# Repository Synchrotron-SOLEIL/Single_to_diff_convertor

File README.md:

Single to Differential Convertors
=================================
Analog Single to Differential Convertors for testing purpose.

Released under GNU GPL license.

Synchrotron SOLEIL's name and logo cannot be used without permission.

----------

http://www.synchrotron-soleil.fr/

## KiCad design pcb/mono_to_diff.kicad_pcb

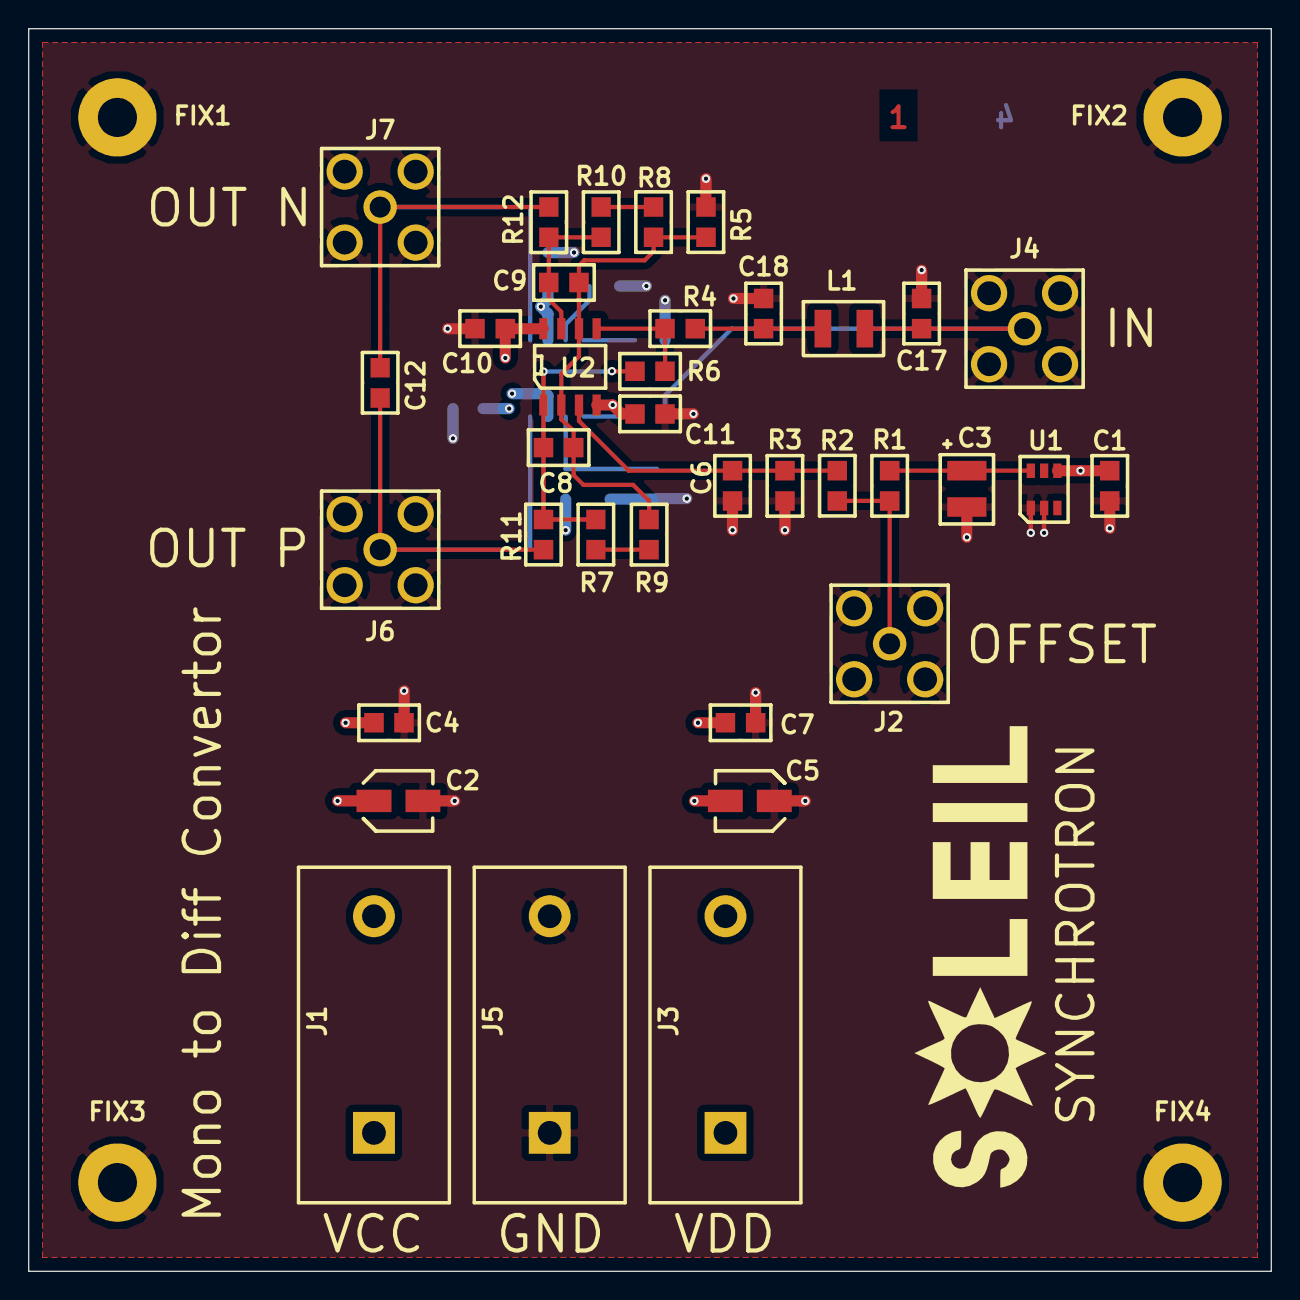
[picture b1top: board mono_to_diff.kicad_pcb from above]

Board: 4 copper layers, 88.9 x 88.9 mm, 51 parts (0 on the bottom side), 22 nets.

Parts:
C1, C10, C11, C12, C15, C16: 10nF-50V-10p-Ceramic-0805; SOLEIL-0805
C2, C5: 10uF-16V-20p-Al-TypeB; SOLEIL-TYPEB
C3: 2u2F-20V-10p-Tantalum-1210; SOLEIL-PC-B
C4, C7, C13, C14: 100nF-50V-10p-Ceramic-0805; SOLEIL-0805
C6: 1nF-50V-10p-Ceramic-0805; SOLEIL-0805
C8, C9: 5pF-50V-10p-Ceramic-0805; SOLEIL-0805
C17, C18: 2200pF-50V-5p-Ceramic-0805; SOLEIL-0805
FIX1, FIX2, FIX3, FIX4: D_2mm8; SOLEIL-D_2mm8
J1: 24.243.1; SOLEIL-24_243
J2, J4, J6, J7: 132134; SOLEIL-SMA-132134
J3: 24.243.5; SOLEIL-24_243
J5: 24.243.2; SOLEIL-24_243
L1: 10uH-140mA-5p-36MHz-1210; SOLEIL-1210
R1, R17, R18: 0R-0.125W-1P-0805; SOLEIL-0805
R2: 2K37-0.125W-1P-0805; SOLEIL-0805
R3, R14: 1K-0.125W-1P-0805; SOLEIL-0805
R4: 2K2-0.125W-1P-0805; SOLEIL-0805
R5: 470R-0.125W-1P-0805; SOLEIL-0805
R6: 499R-0.125W-1P-0805; SOLEIL-0805
R7, R8: 215R-0.125W-1P-0805; SOLEIL-0805
R9, R10: 1R2-0.125W-1P-0805; SOLEIL-0805
R11, R12: 51R-0.125W-1P-0805; SOLEIL-0805
R13: 1K87-0.125W-1P-0805; SOLEIL-0805
R15, R16: 1K58-0.125W-1P-0805; SOLEIL-0805
U1: LT6656ACS6-1.25; SOLEIL-SOT23-6
U2: LTC6241HVCS8; SOLEIL-SOIC8NB
U3: LT6600CS8-2.5; SOLEIL-SOIC8NB

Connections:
/OUT_N: C12.2, J7.1, R12.1, R18.2
/OUT_P: C12.1, J6.1, R11.1, R17.2
GND: C1.2, C2.2, C3.2, C4.2, C5.1, C6.2, C7.2, C10.2, C11.2, C13.2, C14.2, C15.2, C16.2, C17.2, C18.2, FIX1.1, FIX2.1, FIX3.1, FIX4.1, J2.2, J2.3, J2.4, J2.5, J4.2, J4.3, J4.4, J4.5, J5.1, J5.2, J6.2, J6.3, J6.4, J6.5, J7.2, J7.3, J7.4, J7.5, R3.2, R5.2, R14.2, R16.1, U1.1, U1.2
unnamed: C3.1, R1.1, U1.6
unnamed: C6.1, R2.2, R3.1, U2.3
unnamed: C8.1, R6.1, R9.2, R11.2, U2.1
unnamed: C8.2, C9.2, R5.1, R7.1, R8.1, U2.2, U2.6
unnamed: C9.1, R10.2, R12.2, U2.7
unnamed: C13.1, R13.2, R14.1, U3.2
unnamed: C14.1, U3.7
unnamed: C17.1, J4.1, L1.1, R15.1
unnamed: C18.1, L1.2, R4.2
unnamed: J2.1, R1.2, R2.1
unnamed: R4.1, R6.2, U2.5
unnamed: R7.2, R9.1
unnamed: R8.2, R10.1
unnamed: R15.2, U3.1
unnamed: R16.2, U3.8
unnamed: R17.1, U3.4
unnamed: R18.1, U3.5
VCC: C1.1, C2.1, C4.1, C10.1, C15.1, J1.1, J1.2, R13.1, U1.4, U2.8, U3.3
VDD: C5.2, C7.1, C11.1, C16.1, J3.1, J3.2, U2.4, U3.6

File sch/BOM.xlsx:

Single to Differential Convertors
JP Ricaud
42179
Ref | Manufacturer | Manufacturer ref | Supplier | Supplier ref | Value | Description 1 | Description 1 | Description 3 | Case | Price | Qty
L1 | Panasonic | ELJFA100JF | Farnell | 1198456 | 10uH | 140mA | 5% | 36MHz | 1210 | 0.09 | 1
C13 | KEMET | C0805F104K5RACTU | Farnell | 1288272RL | 100nF | 50V | 10% | X7R | 0805 | 0.28000000000000003 | 1
C14 | KEMET | C0805F104K5RACTU | Farnell | 1288272RL | 100nF | 50V | 10% | X7R | 0805 | 0.28000000000000003 | 1
C4 | KEMET | C0805F104K5RACTU | Farnell | 1288272RL | 100nF | 50V | 10% | X7R | 0805 | 0.28000000000000003 | 1
C7 | KEMET | C0805F104K5RACTU | Farnell | 1288272RL | 100nF | 50V | 10% | X7R | 0805 | 0.28000000000000003 | 1
U2 | LINEAR TECHNOLOGY | LTC6241HVCS8#PBF | Farnell | 1330970 |  | - | - | - | SOIC8 | 5.28 | 1
C6 | KEMET | C0805C102K5RACTU | Farnell | 1414660 | 1nF | 50V | 10% | X7R | 0805 | 3.2000000000000001E-2 | 1
C1 | KEMET | C0805C103K5RACTU | Farnell | 1414662 | 10nF | 50V | 10% | X7R | 0805 | 3.2000000000000001E-2 | 1
C10 | KEMET | C0805C103K5RACTU | Farnell | 1414662 | 10nF | 50V | 10% | X7R | 0805 | 3.2000000000000001E-2 | 1
C11 | KEMET | C0805C103K5RACTU | Farnell | 1414662 | 10nF | 50V | 10% | X7R | 0805 | 3.2000000000000001E-2 | 1
C12 | KEMET | C0805C103K5RACTU | Farnell | 1414662 | 10nF | 50V | 10% | X7R | 0805 | 3.2000000000000001E-2 | 0
C15 | KEMET | C0805C103K5RACTU | Farnell | 1414662 | 10nF | 50V | 10% | X7R | 0805 | 3.2000000000000001E-2 | 1
C16 | KEMET | C0805C103K5RACTU | Farnell | 1414662 | 10nF | 50V | 10% | X7R | 0805 | 3.2000000000000001E-2 | 1
R1 | Vishay | CRCW08050000Z0EA | Farnell | 1469846RL | 0R | 0.125W | 1% | Thick Film | 0805 | 2.1000000000000001E-2 | 1
R17 | Vishay | CRCW08050000Z0EA | Farnell | 1469846RL | 0R | 0.125W | 1% | Thick Film | 0805 | 2.1000000000000001E-2 | 1
R18 | Vishay | CRCW08050000Z0EA | Farnell | 1469846RL | 0R | 0.125W | 1% | Thick Film | 0805 | 2.1000000000000001E-2 | 1
R4 | Vishay | CRCW08052K20FKEA | Farnell | 1469887RL | 2K2 | 0.125W | 1% | Thick Film | 0805 | 2.1999999999999999E-2 | 1
R5 | Vishay | CRCW0805470RFKEA | Farnell | 1469932 | 470R | 0.125W | 1% | Thick Film | 0805 | 2.1999999999999999E-2 | 1
R6 | Vishay | CRCW0805499RFKEA | Farnell | 1469936 | 499R | 0.125W | 1% | Thick Film | 0805 | 2.1999999999999999E-2 | 1
R11 | Vishay | CRCW080551R0FKEA | Farnell | 1469944 | 51R | 0.125W | 1% | Thick Film | 0805 | 2.1999999999999999E-2 | 1
R12 | Vishay | CRCW080551R0FKEA | Farnell | 1469944 | 51R | 0.125W | 1% | Thick Film | 0805 | 2.1999999999999999E-2 | 1
R13 | Vishay | CRCW08051K87FKEA | Farnell | 1652945 | 1K87 | 0.125W | 1% | Thick Film | 0805 | 2.3E-2 | 0
R2 | Vishay | CRCW08052K37FKEA | Farnell | 1652974 | 2K37 | 0.125W | 1% | Thick Film | 0805 | 2.1999999999999999E-2 | 1
U3 | Linear Technology | LT6600CS8-2.5 | Farnell | 1663590 |  | - | - | - | SOIC8 | 7.11 | 1
J1 | Multicomp | 24.243.1 | Farnell | 1698982 | Red | - | - | - | Multicomp 24.243 | 1.76 | 1
J5 | Multicomp | 24.243.2 | Farnell | 1698983 | Black | - | - | - | Multicomp 24.243 | 1.83 | 1
J3 | Multicomp | 24.243.5 | Farnell | 1698984 | Blue | - | - | - | Multicomp 24.243 | 0.81 | 1
C8 | Multicomp | MC0805N5R0C500CT | Farnell | 1759184 | 5pF | 50V | 5% | C0G | 0805 | 4.1000000000000002E-2 | 1
C9 | Multicomp | MC0805N5R0C500CT | Farnell | 1759184 | 5pF | 50V | 5% | C0G | 0805 | 4.1000000000000002E-2 | 0
U1 | Linear Technology | LT6656ACS6-1.25#TRMPBF | Farnell | 1839079 | 1.25V | - | - | - | SOT23-6 | 7.22 | 1
C3 | AVX | TAJB225K020RNJ | Farnell | 197373RL | 2.2uF | 20V | 10% | Tantalum | 1210 | 0.22 | 1
C17 | KEMET | C0805C222J5GACAUTO | Farnell | 2070464 | 2200pF | 50V | 5% | C0G | 0805 | 0.1 | 0
C18 | KEMET | C0805C222J5GACAUTO | Farnell | 2070464 | 2200pF | 50V | 5% | C0G | 0805 | 0.1 | 0
J2 | Amphenol Connex | 132134 | Farnell | 2112465 | - | - | - | - | SMA 132134 | 3.65 | 1
J4 | Amphenol Connex | 132134 | Farnell | 2112465 | - | - | - | - | SMA 132134 | 3.65 | 1
J6 | Amphenol Connex | 132134 | Farnell | 2112465 | - | - | - | - | SMA 132134 | 3.65 | 1
J7 | Amphenol Connex | 132134 | Farnell | 2112465 | - | - | - | - | SMA 132134 | 3.65 | 1
R7 | Vishay | CRCW0805215RFKEA | Farnell | 2138869 | 215R | 0.125W | 1% | Thick Film | 0805 | 2.1999999999999999E-2 | 1
R8 | Vishay | CRCW0805215RFKEA | Farnell | 2138869 | 215R | 0.125W | 1% | Thick Film | 0805 | 2.1999999999999999E-2 | 1
R15 | Vishay | CRCW08051K58FKEA | Farnell | 2138936 | 1K58 | 0.125W | 1% | Thick Film | 0805 | 1.2E-2 | 1
R16 | Vishay | CRCW08051K58FKEA | Farnell | 2138936 | 1K58 | 0.125W | 1% | Thick Film | 0805 | 1.2E-2 | 1
R10 | Panasonic | ERJB1BF1R2U | Farnell | 2294005 | 1R2 | 0.125W | 1% | Thick Film | 0805 | 0.47899999999999998 | 1
R9 | Panasonic | ERJB1BF1R2U | Farnell | 2294005 | 1R2 | 0.125W | 1% | Thick Film | 0805 | 0.47899999999999998 | 1
R14 | Yageo | RC0805FR-071KL | Farnell | 9237496RL | 1K | 0.125W | 1% | Thick Film | 0805 | 1.7000000000000001E-2 | 1
R3 | Yageo | RC0805FR-071KL | Farnell | 9237496RL | 1K | 0.125W | 1% | Thick Film | 0805 | 1.7000000000000001E-2 | 1
C2 | Panasonic | EEEFC1C100R | Farnell | 9693491 | 10uF | 16V | 20% | Aluminium | Type B | 0.31 | 1
C5 | Panasonic | EEEFC1C100R | Farnell | 9693491 | 10uF | 16V | 20% | Aluminium | Type B | 0.31 | 1

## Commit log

2015-06-12 First commit
    On branch master
    Changes to be committed:
    new file: sch/mono_to_diff-cache.lib
    new file: sch/mono_to_diff-rescue.lib
    new file: sch/mono_to_diff.pro
    new file: sch/mono_to_diff.sch
2015-06-19 First commit
    On branch development
    new file: README.md
    renamed: sch/mono_to_diff.pro -> mono_to_diff.pro
    new file: pcb/mono_to_diff.kicad_pcb
    new file: pcb/mono_to_diff.net
    new file: pcb/mono_to_diff.pro
2015-06-22 PCB routed
    On branch development
    modified: pcb/mono_to_diff.kicad_pcb
    modified: pcb/mono_to_diff.pro
2015-06-23 Added a low pass filter
    On branch development
    modified: pcb/mono_to_diff.kicad_pcb
    modified: pcb/mono_to_diff.net
    modified: sch/mono_to_diff-cache.lib
    modified: sch/mono_to_diff.pro
    modified: sch/mono_to_diff.sch
2015-06-24 PCB finished
    On branch development
    modified: README.md
    new file: pcb/gerber/mono_to_diff-Bottom-4_Cu.gbl
    new file: pcb/gerber/mono_to_diff-Bottom-4_Mask.gbs
    new file: pcb/gerber/mono_to_diff-Bottom-4_Paste.gbp
    new file: pcb/gerber/mono_to_diff-Bottom-4_SilkS.gbo
2015-06-25 Added BOM. Prepared files for fabrication.
    On branch development
    renamed: pcb/gerber/mono_to_diff-bottom.pos -> pcb/gerber/mono_to_diff-Bottom-4.pos
    renamed: pcb/gerber/mono_to_diff-top.pos -> pcb/gerber/mono_to_diff-Top-1.pos
    modified: pcb/gerber/mono_to_diff-drl_map.gbr
    modified: pcb/gerber/mono_to_diff.drl
    new file: sch/BOM.xlsx
